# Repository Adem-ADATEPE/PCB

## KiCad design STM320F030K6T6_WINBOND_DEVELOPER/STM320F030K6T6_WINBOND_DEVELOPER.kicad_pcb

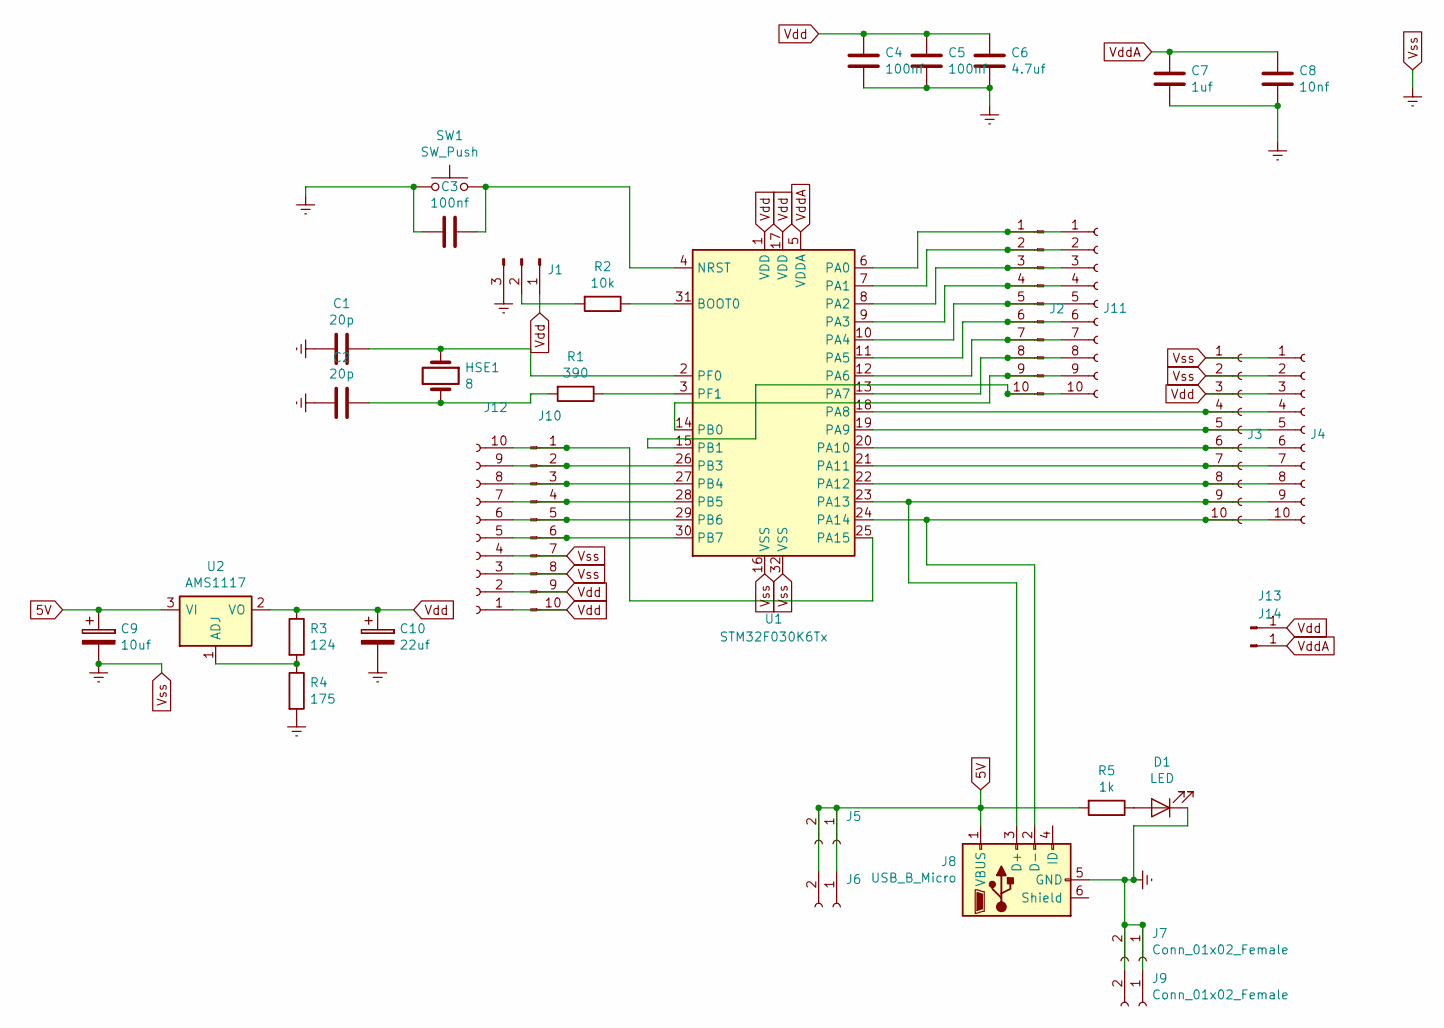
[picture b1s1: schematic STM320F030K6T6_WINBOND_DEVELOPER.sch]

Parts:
C1, C2: 20p; C_1206_3216Metric
C3, C4, C5: 100nf; C_1206_3216Metric
C6: 4.7uf; C_1206_3216Metric
C7: 1uf; C_1206_3216Metric
C8: 10nf; C_1206_3216Metric
C9: 10uf; CP_Elec_6.3x4.5
C10: 22uf; CP_Elec_6.3x4.5
D1: LED; LED_1206_3216Metric
HSE1: 8; Crystal_HC49-4H_Vertical
J1: Conn_01x03_Male; PinHeader_1x03_P2.54mm_Vertical
J2, J10: Conn_01x10_Male; PinSocket_1x10_P2.54mm_Vertical
J3, J11, J12: Conn_01x10_Female; PinHeader_1x10_P2.54mm_Vertical
J4: Conn_01x10_Female; PinSocket_1x10_P2.54mm_Vertical
J5, J7: Conn_01x02_Female; PinHeader_1x02_P2.54mm_Vertical
J6, J9: Conn_01x02_Female; PinSocket_1x02_P2.54mm_Vertical
J8: USB_B_Micro; USB_Micro-B_Amphenol_10103594-0001LF_Horizontal
J13, J14: Conn_01x01_Male; PinHeader_1x01_P2.54mm_Vertical
R1: 390; R_1206_3216Metric
R2: 10k; R_1206_3216Metric
R3: 124; R_1206_3216Metric
R4: 175; R_1206_3216Metric
R5: 1k; R_1206_3216Metric
SW1: SW_Push; SW_SPST_TL3305A
U1: STM32F030K6Tx; LQFP-32_7x7mm_P0.8mm
U2: AMS1117; SOT-223-3_TabPin2

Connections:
5V: C9.1, J5.1, J5.2, J6.1, J6.2, J8.1 (VBUS), R5.2, U2.3 (VI)
unnamed: C1.1, HSE1.1, U1.2 (PF0)
unnamed: C2.1, HSE1.2, R1.2
unnamed: C3.1, SW1.2, U1.4 (NRST)
unnamed: D1.2 (A), R5.1
unnamed: J1.2, R2.2
unnamed: J3.4, J4.4, U1.18 (PA8)
unnamed: J3.5, J4.5, U1.19 (PA9)
unnamed: J3.6, J4.6, U1.20 (PA10)
unnamed: J3.7, J4.7, U1.21 (PA11)
unnamed: J3.8, J4.8, U1.22 (PA12)
unnamed: J3.9, J4.9, J8.3 (D+), U1.23 (PA13)
unnamed: J3.10, J4.10, J8.2 (D-), U1.24 (PA14)
unnamed: J10.1, J12.10, U1.25 (PA15)
unnamed: J10.2, J12.9, U1.26 (PB3)
unnamed: J10.3, J12.8, U1.27 (PB4)
unnamed: J10.4, J12.7, U1.28 (PB5)
unnamed: J10.5, J12.6, U1.29 (PB6)
unnamed: J10.6, J12.5, U1.30 (PB7)
unnamed: J2.1, J11.1, U1.6 (PA0)
unnamed: J2.2, J11.2, U1.7 (PA1)
unnamed: J2.3, J11.3, U1.8 (PA2)
unnamed: J2.4, J11.4, U1.9 (PA3)
unnamed: J2.5, J11.5, U1.10 (PA4)
unnamed: J2.6, J11.6, U1.11 (PA5)
unnamed: J2.7, J11.7, U1.12 (PA6)
unnamed: J2.8, J11.8, U1.13 (PA7)
unnamed: J2.9, J11.9, U1.14 (PB0)
unnamed: J2.10, J11.10, U1.15 (PB1)
unnamed: R1.1, U1.3 (PF1)
unnamed: R2.1, U1.31 (BOOT0)
unnamed: R3.2, R4.1, U2.1 (ADJ)
Vdd: C4.1, C5.1, C6.1, C10.1, J1.1, J3.3, J4.3, J10.9, J10.10, J12.1, J12.2, J13.1, R3.1, U1.1 (VDD), U1.17 (VDD), U2.2 (VO)
VddA: C7.1, C8.1, J14.1, U1.5 (VDDA)
Vss: C1.2, C2.2, C3.2, C4.2, C5.2, C6.2, C7.2, C8.2, C9.2, C10.2, D1.1 (K), J1.3, J3.1, J3.2, J4.1, J4.2, J7.1, J7.2, J8.5 (GND), J9.1, J9.2, J10.7, J10.8, J12.3, J12.4, R4.2, SW1.1, U1.16 (VSS), U1.32 (VSS)

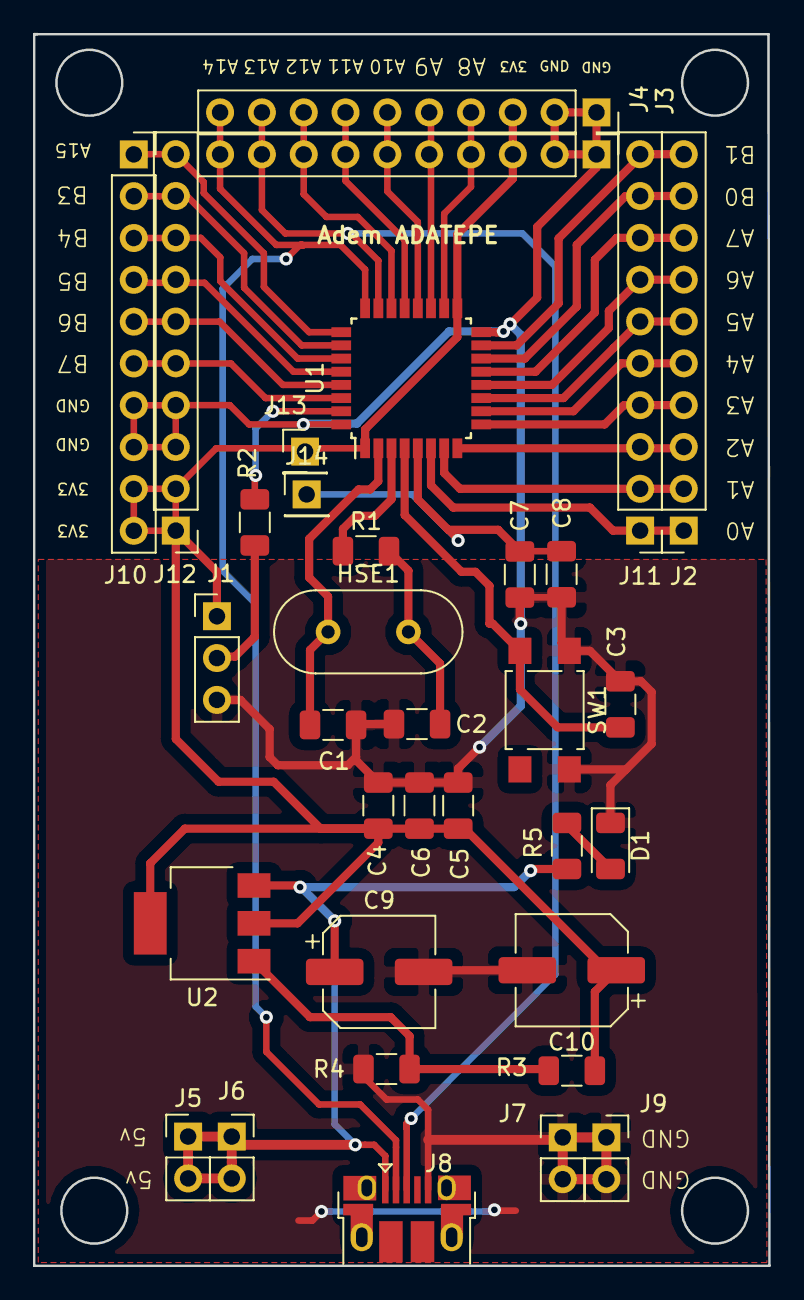
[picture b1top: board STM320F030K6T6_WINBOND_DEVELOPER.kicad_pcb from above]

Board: 2 copper layers, 44.7 x 74.8 mm, 34 parts (0 on the bottom side), 35 nets.

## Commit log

2021-01-23 stm32f030k6t6
